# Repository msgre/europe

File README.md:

Europe is interactive knowledge game for children.

**Content**:

* [Construction](#construction)
    * [Gameboard](#gameboard)
    * [Hardware](#hardware)
    * [Software](#software)
    * [Design](#design)
    * [Content](#content)
* [Docker](#docker)
    * [Build](#build)
    * [Run](#run)
* [Application](#application)
    * [Game interface](#game-interface)
    * [Administration interface](#administration-interface)
* [Notes](#notes)
    * [Database initialization](#database-initialization)
    * [Coffeescript compilation](#coffeescript-compilation)
    * [LESS compilation](#less-compilation)
    * [Debug mode for Javascript application](#debug-mode-for-javascript-application)

# Construction

It is constructed from several parts:

* big wooden gameboard with map of Europe
* bunch of electronics
* software

## Gameboard

Board will be connected to the ground via spring, so children will be able to 
tilt it. Each european country will have gate on his territory. 

## Hardware

Each gate is constructed as optical sensor. On bottom part of board is 10
control boards, each of them capable to read state up to 6 sensors. Boards are
interconnected via ModBus.

There are additional 2 special boards -- one of them will serve as keyboard
(instead of optical sensors it will read state from buttons), second as 
controller of Neopixels RGB LED.

Details about hardware solution is stored in [`hardware/`](hardware) directory.

## Software

ModBus is connected through USB adapter to Intel NUC miniPC with Ubuntu Linux
and all necessary software:

* Django API backend
* Django Admin backend
* Python Watcher script, which read status from HW boards and send events
  through websocket connection to browser
* Frontend Javascript application build in Marionette framework

All components are dockerized and run behind Nginx proxy.

There are several subdirectories in regards to software part of this project:

* [`ansible/`](ansible)  
  Playbooks for bootstraping Ubuntu system (it will turn plain Ubuntu into 
  Evropa dedicated machine)
* [`europe/`](europe)  
  Django backend application, which realise API interface and administration
  for editing content (game questions)
* [`static/`](static)  
  Frontend Javascript application
* [`watcher/`](watecher)  
  Python3 application communicating with hardware (ModBus via USB) and implementing
  websockets server. Frontend Javascript application communicate with HW in
  real-time via messages sent over websocket.

## Design

Application design evolve in time. You could found some of the designs in 
[`screenshots/`](screenshots) directory. In [`layouts/`](layouts) is stored 
rough HTML version of early version application for easier CSS development.

## Content

Content of the game (questions about european countries) will be edited via
web administration. For easier development there are some of the content
store in directory [`content/`](content).

# Docker

There are several Dockerfiles in root directory, suffix indicate purpose of
file. Because there are lot of them, and running them manually from commandline
could be complicated, we use Docker Compose.

Main description is stored in [`docker-compose.yml`](docker-compose.yml).
According to [Docker Compose documentation](https://docs.docker.com/compose/extends/), 
there is standard way how to extend basic yml and adapt it to different
environments (notebook, Intel NUC, demo on Digital Ocean). This variants are
stored as `docker-compose.<ENV>.yml` files. To apply it, choose one, copy it or
make a named symlink `docker-compose.override.yml` (I personally use `devel`
variant on my notebook).

## Build

Run this commands:

    docker build -f Dockerfile.base -t msgre/common:europe-base.latest .
    docker-compose build
    cd watcher/ && docker build -t msgre/common:europe-watcher.latest .

`base` is general Django container, `watcher` take care about HW monitoring
and publish events on websockets.

## Run

    docker-compose up -d
    docker-compose logs

To kill and remove running containers, run:

    docker-compose kill && docker-compose rm -f

Beware! If you run Europe for first time, you must initiate database. See
[Database initialization](#database-initialization) below.

# Application

## Game interface

Open in **Chrome** browser URL http://192.168.99.100:8081/
(warning, doesn't work properly in Firefox due to disfunctional keyboard plugin).

For controling web app use following keys (they will be replaced in final 
product to real physical keys):

* `Q` = left
* `W` = right
* `P` = choice

During game phase, use:

* `0` = wrong answer
* `1` = right answer

If you run `watcher` container in debug mode, you could simulate HW events by
touching files in `watcher/gates` directory. For example:

    touch watcher/gates/14/1

will simulate ball passing gate number 1 on board 14. Same way you could 
simulate keyboard events.

## Administration interface

There is standard Django admin interface on http://192.168.99.100:8081/admin.
You could modify options, questions, and several other details about game.

# Notes

## Database initialization

Connect to already running `admin` container:

    docker exec -ti admin bash

Run following commands:

    ./manage.py migrate
    ./manage.py createsuperuser
    ./manage.py initial_questions /content
    ./manage.py fake_results

After this sequence, your DB schema will be up to date, and will contain
data about superadmin (to access administration via web interface), fake
results data (to bypass results pages with no entries) and initial set of
questions loaded from `content/` directory.

## Coffeescript compilation

First, check that you have CoffeeScript container. If no, build it:

    docker build -f Dockerfile.coffee -t msgre/common:coffee.latest .

One-time Coffeescript to Javascript compilation:

    docker run -ti --rm -v $PWD/static/app:/src msgre/common:coffee.latest -bc /src

Continuous compilation based on changes in watched directory:

    fswatch --exclude="\.js$" -o $PWD/static/app | xargs -n1 -I{} docker run -i --rm -v $PWD/static/app:/src msgre/common:coffee.latest -bc /src

## LESS compilation

One-time compilation:

    docker run -i --rm -v $PWD/static/css:/src ewoutp/lessc:latest /src/styles.less > $PWD/static/css/styles.css

## Debug mode for Javascript application

For debugging purposes you could add special URL parameters to directly enter
one of the Javascript application screens. In this case timeouts (part of code
that return you to initial `intro` page) will be set to very high value, so
you stay on given page for very long time (and you could debug HTML/CSS/JS 
things with peace in mind).

Enter URLs like `http://192.168.99.100:8081/?intro`. Last part after `?` 
character tells in which page you are interested. Enter one of this values:
`intro`, `crossroad`, `scores`, `gamemode`, `countdown`, `game`, `result`, 
`recap`, `score`.

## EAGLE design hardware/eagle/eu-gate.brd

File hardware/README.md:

# Hardware

Europe's hardware consists of two boards -- gate and IR.

To detect active gate the IR board contains reflective IR photointerrupter.
This board has to be powered by 5 VDC, the output signal is 5V (no activity)
or 0V (GND, gate was activated).

Up to six IR boards can be connected to one "gate board". This board can supply
5V to all connected IR gates and register their output signal. Gate board have
to be powered by 5VDC from RS485 bus. The Modbus is used to read status of all
IR gates connected to one gate board.

Each gate board has 4 solder jumpers for Modbus slave address. Their
firmware can be updated via Modbus.

## Overview

- `eagle`, `gerber` and `pdf` -- documentation for manufacturing this hardware.
- `bootloader` -- source code of Modbus bootloader for ATMegaXX8P.
- `src` -- main firmware for gate boards.
- `neopixel` -- control Neopixel (WS2812) LEDs via Modbus.
- `examples` -- simple Python examples, how to control and update gates over Modbus.

## Bootloader and Firmware

To make firmware for AVR the avr-gcc and avrdude is needed. Bootloader and firmware
can be compiled by `make`.

Programming bootloader to connected board (you will need AVRispmkII programmer):

    $ cd bootloader
    $ make
    $ make fuses && make flash

If programming was successful, the green onboard LED should be permanently turned on.
This indicates the bootloader is running and accepting Modbus commands.

Main firmware can be compiled like this:

    $ cd src
    $ make

This will create `main.bin` file which can be used with Modbus bootloader like
this:

    $ ./examples/modbus_update.py /dev/usbserial.XYZ addr ./src/main.bin

## Neopixel Firmware

Special firmware version for interfacing WS2812 LEDs through Modbus is
in directory `neopixel`. This firmware can be compiled the same way as main
firmware:

    $ cd neopixel
    $ make

This special firmware has the same modbus registers as main firmware (inputs,
reset, HW&FW version) and aditional address space `0x1000`. One register in
this space represents one Neopixel LED. The bit mapping is:

    +-------------------------------+-------------------------------+
    |         High byte             |            Low byte           |
    +-------------------------------+-------------------------------+
    | 7 | 6 | 5 | 4 | 3 | 2 | 1 | 0 | 7 | 6 | 5 | 4 | 3 | 2 | 1 | 0 |
    +-------------------------------+-------------------------------+
    | L | L | L | L | R | R | R | R | G | G | G | G | B | B | B | B |
    +-------------------------------+-------------------------------+

where `R` = red, `G` = green, `B` = blue, `L` = brightness. For example:

    0x1F00 = red
    0x10F0 = green
    0x100F = blue
    0x16F0 = yellow
    0x06F0 = yellow, minimum brightness.
    0xF6F0 = yellow, maximum brightness.

Neopixels should be connected to the pin PWM0 (AVR pin PD6).

## Modbus Address

The slave address is selected by solder jumpers SJ1-SJ4. Soldered jumper represent
LOW, thus connecting SJ3 and SJ4 makes address `0x03`.

The bootloader slave address has MSB set -- for example `0x03 -> 0x83`.

## Modbus Registers

Modbus register is 16 bit integer. The firmware has three registers on addresses:

- `0x0000` 0x00XX; IR gates state since last Modbus reading or FW reset.
- `0x0001` 0xXYYY; firmware (Y) and hardware (X) version
- `0x0002` reset; any writes to this register will trigger FW reset in 500ms.

## Python Examples

Tested with Python 2.7, pyserial 3.0.1 and minimalmodbus 0.7.

    $ pip install pyserial
    $ pip install minimalmodbus

To update firmware in board with slave address 15 (0x0F), bootloader address is
143 (0x8F):

    $ cd ./examples
    $ ./modbus_update.py /dev/usbserial.XYZ 15 ./firmware.bin

To read latest gate states from board with slave address 15 (0x0F):

    $ ./examples/modbus_read.py /dev/usbserial.XYZ 15

Slave dicovery on bus can be done by:

    $ ./examples/modbus_discover.py /dev/usbserial.XYZ

To use neopixel firmware on slave 13 (example expects 24 WS2812 LEDs):

    $ ./examples/neopixel_rainbow.py /dev/usbserial.XYZ 13

## Wires

There are two types of wires.

First wire is for RS485/Modbus and connects
together gate boards. This should be at least 2 twisted pairs with RJ12 (6p6c) on both
ends. All gate boards are daisy chained from first to last board and to Modbus
master.

Second type of wire connects IR boards with gate boards. This is 3 core flat
cable and 3 pins connectors with 2.54mm (0.1'') pitch. KK254 Molex or NS25 Ninigi
types can be used.

### RS485/Modbus Wires

The cable for RS485 is Ethernet Cat 5e, stranded. Orange and orange/wite pair is not used.

### IR Boards Wires

Prepare flat wire, connector housing and pins.

Crimp pins to wire on both ends. Used crimping tool: Engineer PA-09.

Correct pins orientation on wire.

Finished wire.

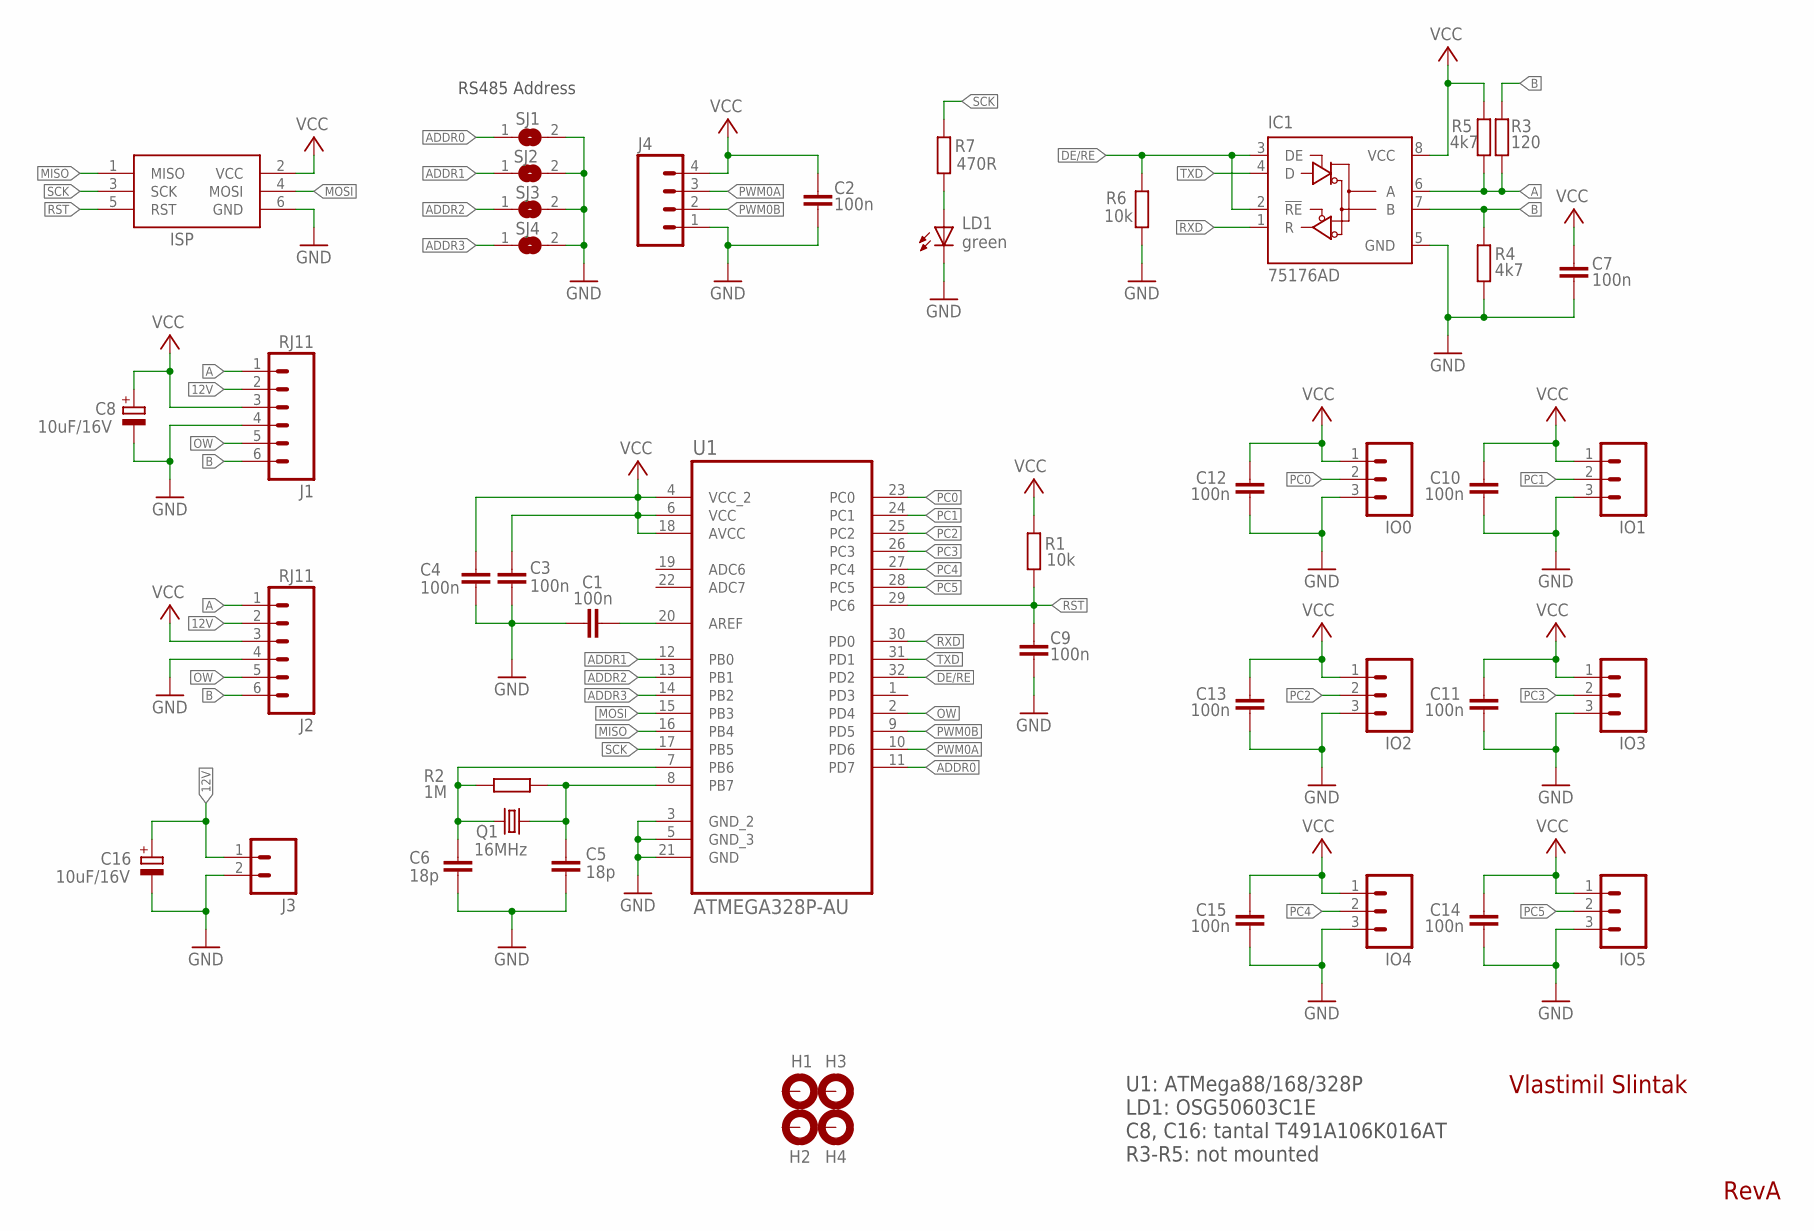
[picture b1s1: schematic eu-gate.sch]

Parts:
C1, C2, C3, C4, C7, C9, C10, C11, C12, C13, C14, C15: 100n; C0603
C5, C6: 18p; C0603
C8, C16: 10uF/16V; SMC_A
H1, H2, H3, H4: MOUNT-PAD-ROUND3.0; 3,0-PAD
IC1: 75176AD; D_R-PDSO-G8
IO0, IO1, IO2, IO3, IO4, IO5: M03POLAR; MOLEX-1X3
ISP: AVRISP-6; AVRISP
J1, J2: RJ11; RJ11-6
J3: M02POLAR; MOLEX-1X2
J4: M04POLAR; MOLEX-1X4
LD1: green; CHIPLED_0603
Q1: 16MHz; HC49UP
R1, R6: 10k; R0603
R2: 1M; R0603
R3: 120; R0603
R4, R5: 4k7; R0603
R7: 470R; R0603
SJ1, SJ2, SJ3, SJ4: SJ
U1: ATMEGA328P-AU; 32TQFP

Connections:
12V: C16.+, J1.2, J2.2, J3.1
A: IC1.6 (A), J1.1, J2.1, R3.2, R5.1
ADDR0: SJ1.1, U1.11 (PD7)
ADDR1: SJ2.1, U1.12 (PB0)
ADDR2: SJ3.1, U1.13 (PB1)
ADDR3: SJ4.1, U1.14 (PB2)
B: IC1.7 (B), J1.6, J2.6, R3.1, R4.2
DE/RE: IC1.2 (!RE), IC1.3 (DE), R6.2, U1.32 (PD2)
GND: C1.1, C2.1, C3.1, C4.1, C5.2, C6.2, C7.2, C8.-, C9.1, C10.1, C11.1, C12.1, C13.1, C14.1, C15.1, C16.-, IC1.5 (GND), IO0.3, IO1.3, IO2.3, IO3.3, IO4.3, IO5.3, ISP.6 (GND), J1.4, J2.4, J3.2, J4.1, LD1.C, R4.1, R6.1, SJ1.2, SJ2.2, SJ3.2, SJ4.2, U1.3 (GND_2), U1.5 (GND_3), U1.21 (GND)
MISO: ISP.1 (MISO), U1.16 (PB4)
MOSI: ISP.4 (MOSI), U1.15 (PB3)
unnamed: C1.2, U1.20 (AREF)
unnamed: LD1.A, R7.1
unnamed: C5.1, Q1.1, R2.2, U1.8 (PB7)
OW: J1.5, J2.5, U1.2 (PD4)
PC0: IO0.2, U1.23 (PC0)
PC1: IO1.2, U1.24 (PC1)
PC2: IO2.2, U1.25 (PC2)
PC3: IO3.2, U1.26 (PC3)
PC4: IO4.2, U1.27 (PC4)
PC5: IO5.2, U1.28 (PC5)
PWM0A: J4.3, U1.10 (PD6)
PWM0B: J4.2, U1.9 (PD5)
RST: C9.2, ISP.5 (RST), R1.1, U1.29 (PC6)
RXD: IC1.1 (R), U1.30 (PD0)
SCK: ISP.3 (SCK), R7.2, U1.17 (PB5)
TXD: IC1.4 (D), U1.31 (PD1)
VCC: C2.2, C3.2, C4.2, C7.1, C8.+, C10.2, C11.2, C12.2, C13.2, C14.2, C15.2, IC1.8 (VCC), IO0.1, IO1.1, IO2.1, IO3.1, IO4.1, IO5.1, ISP.2 (VCC), J1.3, J2.3, J4.4, R1.2, R5.2, U1.4 (VCC_2), U1.6 (VCC), U1.18 (AVCC)
XYZ: C6.1, Q1.2, R2.1, U1.7 (PB6)

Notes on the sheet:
R3-R5: not mounted
C8, C16: tantal T491A106K016AT
LD1: OSG50603C1E
RS485 Address
U1: ATMega88/168/328P

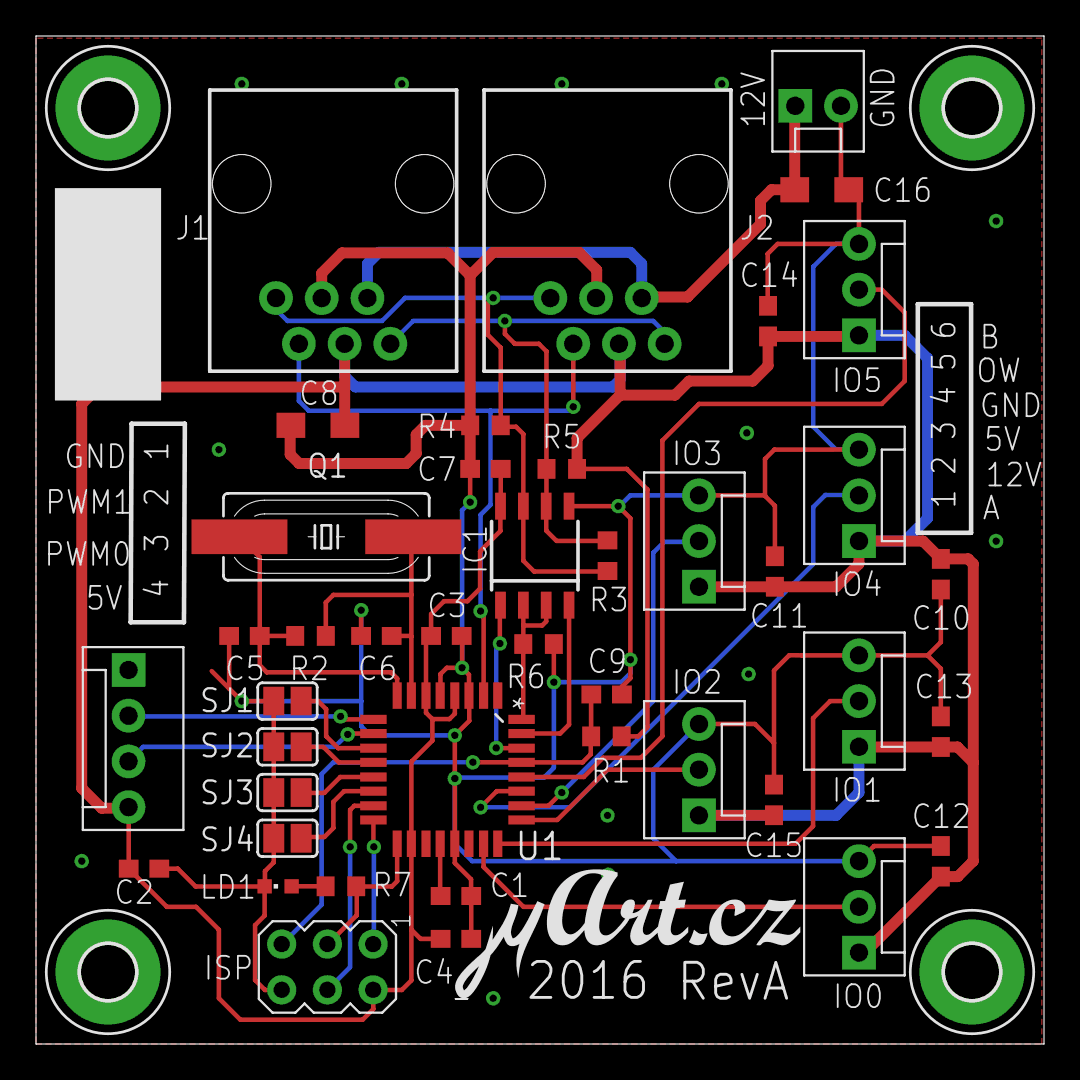
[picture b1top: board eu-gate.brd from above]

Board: 2 copper layers, 56.0 x 56.0 mm, 47 parts (0 on the bottom side), 29 nets.

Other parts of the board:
U$1: UART-LOGO

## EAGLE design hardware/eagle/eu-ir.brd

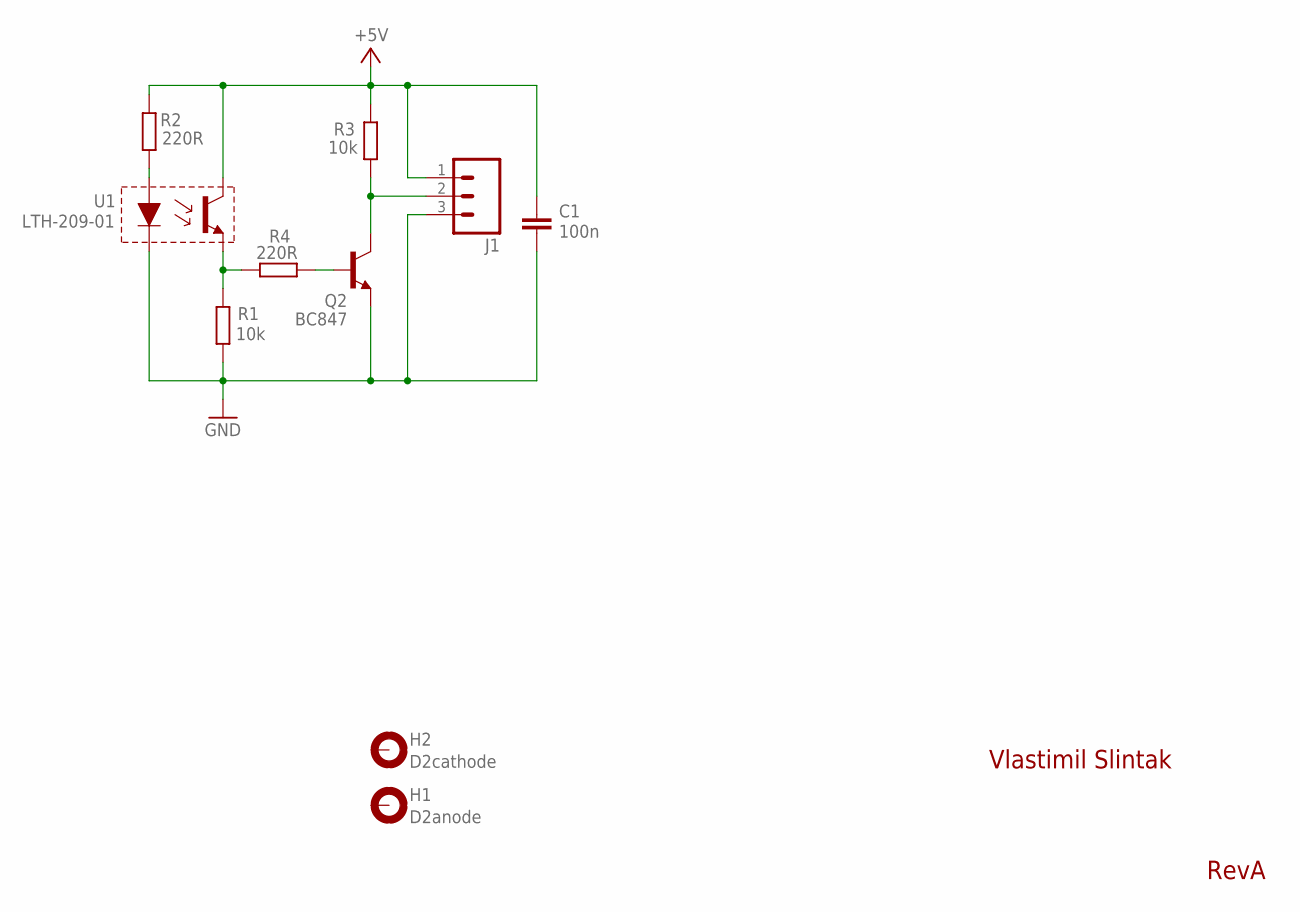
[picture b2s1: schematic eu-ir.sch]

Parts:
C1: 100n; C0603
H1: D2anode; 4,1-PAD
H2: D2cathode; 4,1-PAD
J1: M03POLAR; MOLEX-1X3
Q2: BC847; SOT23
R1, R3: 10k; R0603
R2, R4: 220R; R0603
U1: LTH-209-01; LTH209

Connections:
+5V: C1.1, J1.1, R2.2, R3.1, U1.T4 (C)
GND: C1.2, J1.3, Q2.2 (E), R1.1, U1.D2 (D-)
unnamed: R2.1, U1.D1 (D+)
unnamed: R1.2, R4.2, U1.T3 (E)
unnamed: J1.2, Q2.3 (C), R3.2
unnamed: Q2.1 (B), R4.1

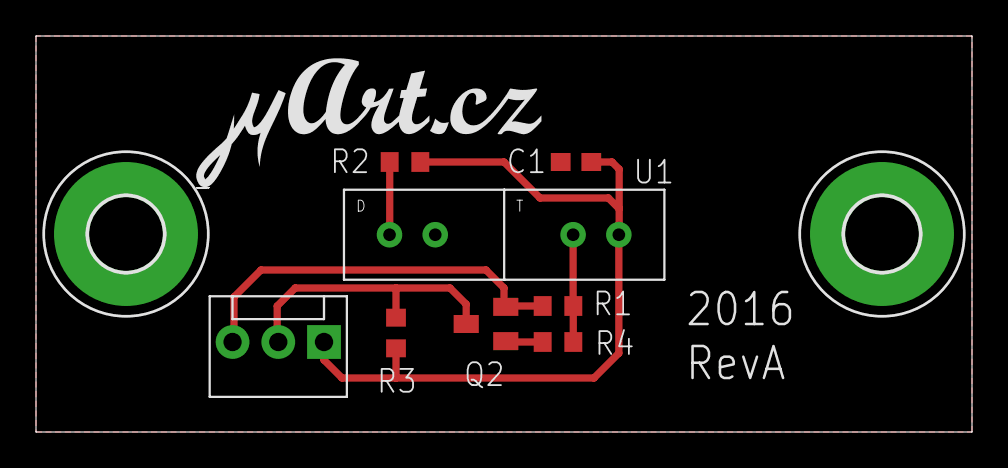
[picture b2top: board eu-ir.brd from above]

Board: 2 copper layers, 52.0 x 22.0 mm, 11 parts (0 on the bottom side), 6 nets.

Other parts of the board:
U$1: UART-LOGO

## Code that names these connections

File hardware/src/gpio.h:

#ifndef __EU_GPIO_H__
#define __EU_GPIO_H__

// Onboard green LED.
#define LED_GRN PB5
#define LED_INIT() DDRB |= _BV(LED_GRN)
#define LED_ON()   PORTB |= _BV(LED_GRN)
#define LED_OFF()  PORTB &= ~_BV(LED_GRN)
#define LED_TOGGLE() PORTB ^= _BV(LED_GRN)

// Pin definitions for all 6 inputs.
#define IR_DDR  DDRC
#define IR_PIN  PINC
#define IR_PORT PORTC
#define IR_IOS  0x3F
#define IR_IO0  _BV(PC0)
#define IR_IO1  _BV(PC1)
#define IR_IO2  _BV(PC2)
#define IR_IO3  _BV(PC3)
#define IR_IO4  _BV(PC4)
#define IR_IO5  _BV(PC5)
#define IR_ALL  (IR_IO0 | IR_IO1 | IR_IO2 | IR_IO3 | IR_IO4 | IR_IO5)
// Set all pins as output and activate pullups.
#define IR_INIT() IR_DDR &= ~IR_ALL; IR_PORT |= IR_ALL


#define PCINT_ENABLE()  (PCICR |= _BV(PCIE1))
#define PCINT_DISABLE() (PCICR &= ~_BV(PCIE1))

/**
 * Initialize all inputs and enable pinchange interrupt.
 */
void gpio_init(void);

/**
 * Read states of all inputs and debouncing.
 */
uint8_t gpio_loop(void);

#endif

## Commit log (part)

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2015-02-17 Missing record in Country
2015-02-17 Helper initial data for quiz, countries capitals
2015-02-18 Added API to basic endpoints
2015-02-19 Docker support -- now it is possible to build runtime Python image and run application in container
2015-02-20 Docker tuning
2015-02-22 Updated Docker sckripts and configs. Now we have functional Nginx container, which serve API from Django app and frontend JS scripts on same domain.
2015-02-22 API endpoints are now prefixed with /api/, turn off API authentification
2015-02-22 First set of frontend JS code (screens #2..#4)
2015-02-24 Category in Questions API response
2015-02-24 Category now have order
2015-02-24 More real initial questions
2015-02-24 More functionality to screen #4 -- event for good/bad tunel, time/progress penalization, stop of the game and final message to console
2015-03-02 New application with game results
2015-03-02 Docker install helper script
2015-03-02 Proof of concept for splitting JS application to many Marionette modules. Realization ~70% of skelet for Europe JS application.
2015-03-02 Added SFX
2015-03-03 Support for saving score results in DB
2015-03-03 Save score on the end of result screen, show scores after that (scores screen not finished yet)
2016-01-16 MQTT communication and WebSocket Javascript client demo
2016-01-16 Custom command for cleaning high scores
2016-01-16 Screenshots of demo application
2016-01-24 Variable time for answering questions according to category
2016-01-24 Small change on metadata of Result model
2016-01-24 Category time and penalty in API response
2016-01-24 API endpoint /api/results now return aggregated minimum times from each category
2016-01-24 Static files compiled with fresh version of CofeeScript
2016-01-24 Added difficulty attribute to Result model
2016-01-24 Page with browsable scores, WIP
2016-01-30 Game difficulty is now taken in account during API calls
2016-01-30 Image support demonstration. Randomly show image on question page.
2016-01-30 Time settings from Category model is now correctly passed into Javascript application, so questions from easy categories have much longer time to answer.
2016-01-30 Correct transfer of options between screens after gamemode change
2016-01-30 Recapitulation screen
2016-01-30 Dockerfiles
2016-01-30 Missing bower_components\? Hm....
2016-01-31 Cleanup in Javascript filenames
2016-01-31 Change of control -- instead up/down we now have left/right/fire mapped to q/w/p keys
2016-01-31 Every module now log notification about his start
2016-01-31 Removed unused Django score application
2016-01-31 API endpoint for results with time now include difficulty, cleanup in Options
2016-02-05 Updated comments in JS modules
2016-02-07 Update of README file
2016-02-07 Updated documentation
2016-02-07 Missing default attribute, cosmetics...
2016-02-07 Version in page footer
2016-02-07 Docker Compose support, now even easier to run entire stack
2016-03-05 First version of HTML pages for Javascript application
2016-03-05 Oops. English version of layouts/README.md
2016-03-05 YAML in requirements
2016-03-06 Explicit names for Docker containers for easier manipulation with Docker compose
2016-03-06 Migrations for backend application -- icon and disabled attribute for quiz.Category model and few data migrations
2016-03-06 Prettyfied HTML for layout
2016-03-10 hardware: eagle schematics for gate and IR boards
2016-03-10 hardware: gerber outputs
2016-03-10 hardware: schematics, assembly documentation and BOM
2016-03-10 hardware: python examples and README
2016-03-11 hardware: wires description in README
2016-03-11 hardware: fixed README syntax
2016-03-11 hardware: comments in Python examples
2016-03-11 hardware: rs485/modbus bootloader
2016-03-14 hardware: firmware for Modbus gate
2016-03-23 Watcher, application watching gate states through ModBus and propagating events through WebSockets to browser.
2016-03-23 There must me small wait between sequential read_registers
2016-03-23 Ooops, mistakenly added obsolete Dockerfile
2016-03-23 Typo in watcher docs
2016-03-23 Subscribe simple HTTP app also to keyboard events
2016-03-25 Narrow game categories to 8
2016-03-25 Gamemode screen with list of categories now allow select only active items
2016-03-25 More realistic variants of photos in game questions. JS code ready, backend tweaked to generate various random image types.
2016-03-25 Modified algorithm for random selection of questions. Countries and their neighbours taken in account.
2016-03-25 Country model now have attributes to identify HW boards on gamedesk -- board and gate ID
2016-03-25 Combined questions needs padding for text
2016-03-26 Timeout is back on gamemode screen
2016-03-26 Optimized demo photos
2016-03-28 hardware: support for ATMega88P MCU and fixed modbus address
2016-03-28 hardware: support for ATMega88P in modbus bootloader
2016-03-28 hardware: Python example for Neopixel firmware, updated README
2016-03-28 hardware: README fixed
2016-03-28 hardware: bootloader and firmware binaries
2016-03-29 DEBUG mode for watcher script. Now it is possible to simulate ball pass events even without access to hardware.
2016-03-30 Autobahn websockets library added to JS app, websocket channel between backend and frontend, commands replaced by triggers
2016-03-30 Relations between containers in docker-compose.yml
2016-03-30 Container with administration, cleanup in settings/urls/wsgi scripts for different containers, docker-compose with build sections
2016-03-30 Note about administration URL
2016-04-01 Administration of Geo model
2016-04-01 Administration of game options
2016-04-01 Administration of quiz models
2016-04-01 Administration of results
2016-04-01 Note about DB constrains on Country model
2016-04-01 Debug mode for Javascript application
2016-04-01 Missing link in main README.md
2016-04-01 Get rid of mqtt code. We are using websockets now for server-frontend communication.
2016-04-01 Docker compose override file for Digital Ocean environment
2016-04-04 More comfortable Django application settings in Dockerfiles
2016-04-04 Working file uploads for questions in Django application.
2016-04-04 Country code for Country model
2016-04-04 Back to normal quiz serializer with real data
2016-04-05 More environments for docker compose
2016-04-05 First step to control NeoPixels in watcher script
2016-04-06 Tuned Neopixel effects on watcher script. Now is possible to raise LED effects with Websocket message.
2016-04-06 Neopixels flash functionality linked to Javascript app
2016-04-06 Functional Neopixels on intro and countdown pages
2016-04-06 Documentation about demo feature of neopixels.py library
2016-04-07 Wrong log formatting in watcher
2016-04-07 Note field for Quiz model
2016-04-08 Clear timeout even of fire event on gamemode screen, closes #31
2016-04-08 High scores on intro page, closes #10
2016-04-08 Save game results just once, closes #1
2016-04-08 Shared object between screens with questions, answers, etc is now correctly reseted at the end of game
2016-04-08 Propagate content/ directory into admin container for easier initialization of DB
2016-04-08 Name of the team is now saved by explicitly selecting check symbol, closes #30
2016-04-08 Initial data, general concept via /content directory and management command, closes #15
2016-04-08 Lightweight immutability of Questions, now it is not possible to delete Question in administration. Questions have enabled flag. Closes #33
2016-04-08 Renamed Category attribute disabled to enabled, closes #34
2016-04-08 Updated README file, cleanup in directory layout
2016-04-10 Content with outlines of european countries.
2016-04-11 SVG icons for categories and buttons in game
2016-04-11 Players must have at least half of correct answers to make record in top scores
2016-04-11 New set of categories
2016-04-11 Logo on homepage, minor visual tweaks
2016-04-11 Icons for 4 new categories
2016-04-11 Category icon on game screen title
2016-04-12 Dynamic load of SECRET_KEY
2016-04-12 Missing countries in initial data for outlines category
2016-04-12 Ooops, fresh crossbar dependencies broke our Docker image, lets pin it.
2016-04-12 Updated Ansible playbooks
2016-04-12 Turn LED off in devel environment of docker-compose
2016-04-13 Misspelled Andorra name
2016-04-13 Game category tweaks
2016-04-13 Initial data for description and curiosity category
2016-04-13 Cleanup
2016-04-13 Bigger line height and margin for textual only questions.
2016-04-13 Modified handling with high scores, solved #36
2016-04-14 Cleanup of result page, closed #21
2016-04-14 Back to slim buttons on gamemode screen
2016-04-14 Polished results screen with dynamic height of boxes
2016-04-14 Dynamic padding on gamemode screen in relation with categories count
2016-04-14 Set correct category icons
2016-04-14 Align results table cell content to right if it is specified
2016-04-14 Yummy typography thanks to Honza's tipi package
2016-04-14 Run tipi only if question have textual part
2016-04-14 Bump to new version
2016-04-16 Debug screen for easier hardware debugging
2016-04-18 Debugging production Neopixel configuration
2016-04-18 Updated list of production boards for watcher script
2016-04-18 Updated migration with production board/gate combination
2016-04-18 Unique combination of board/gate
2016-04-18 Models for 3D prints.
2016-04-18 Renamed folder with 3d objects
2016-04-18 HW related Python packages on base system
2016-04-18 New sounds
2016-04-18 Visual update -- colors, SVG
2016-04-18 Colorfull screen designs
2016-04-19 Maximum height for images is 780px
2016-04-19 Production set of neighbour countries
2016-04-19 Updates sound effects
2016-04-19 Production set of LEDs
2016-04-19 Swapped colors for good/bad answers
2016-04-19 Updated image for watcher
2016-04-19 Bug in debug screen of Javascript application
2016-04-19 LED number for last country fixed
2016-04-20 Visual update -- condensed font replaced with normal, small updates on screens
2016-04-20 Added flag of Kosovo, temporary remove of Serbia outline
2016-04-20 Updated version date
2016-04-20 Updated flags (no white border inside SVG), CSS style attributes in Question model
2016-04-20 Updated note about 3px border in flags
2016-04-20 Fading slideshow on intro page
2016-04-21 Custom inline CSS rules for flag category
2016-04-21 Screenshots of the nee color scheme
2016-04-21 Updated SVG flags
2016-04-21 Updated note about blind maps process
2016-04-21 Dumbness time -- timewindow after passing gate, during any other false gate passing is ignored
2016-04-21 Dumbness tuning
2016-04-21 Question CSS style in admin
2016-04-21 Question shortener for recap screen
2016-04-21 Custom CSS styling for images and blind maps
2016-04-21 Modified CSS on real display. Everything must be bigger, bro.
2016-04-21 Alternative styling of images on recap screen which should take care about wide images
2016-04-21 Ooops. Wrong place for custom inline questions CSS styles.
2016-04-21 Uppercase hint on result page, shorten texts on recap screen
2016-04-22 Final category order
2016-04-22 Intro slideshow for today's opening ceremony
2016-04-22 Thinner loading message
2016-04-22 Timing for game categories
2016-04-22 Less heroic top 10 fake scores
2016-04-22 Option for ignoring tipi on save Question
2016-04-22 Nasty import bug, dictionaries are not immutable\!
2016-04-22 Finalized set of questions for opening ceremony
2016-04-22 Modified timing for categories
2016-04-22 Alternative way for handling keyboard events
2016-04-25 hardware: neopixel FW with 48 LEDs and for ATMega88
2016-04-25 hardware: keyboard mode for GPIO
2016-04-27 Ignore keyboard events during game
2016-04-27 Watcher script now make reboot flag file upon pressing poweroff button on keyboard gate
2016-04-27 Fine tuning of watcher script -- timing of keyboard events, ignore None states
2016-04-27 Change docker compose confs for -- content for all, nuc with enabled LED
2016-05-05 Updated slideshow on intro page
2016-05-05 Infinite moving on result alphabet, by pressing left button on last letter cursor will move to first letter
2016-05-05 More space for players name in score tables.
2016-09-11 hardware: connection of RS485 cable
2017-09-14 admin: Action for enable/disable group of questions

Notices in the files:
parts and their libraries:
SparkFun-Connectors: Licensing: Creative Commons ShareAlike 4.0 International - https://creativecommons.org/licenses/by-sa/4.0
